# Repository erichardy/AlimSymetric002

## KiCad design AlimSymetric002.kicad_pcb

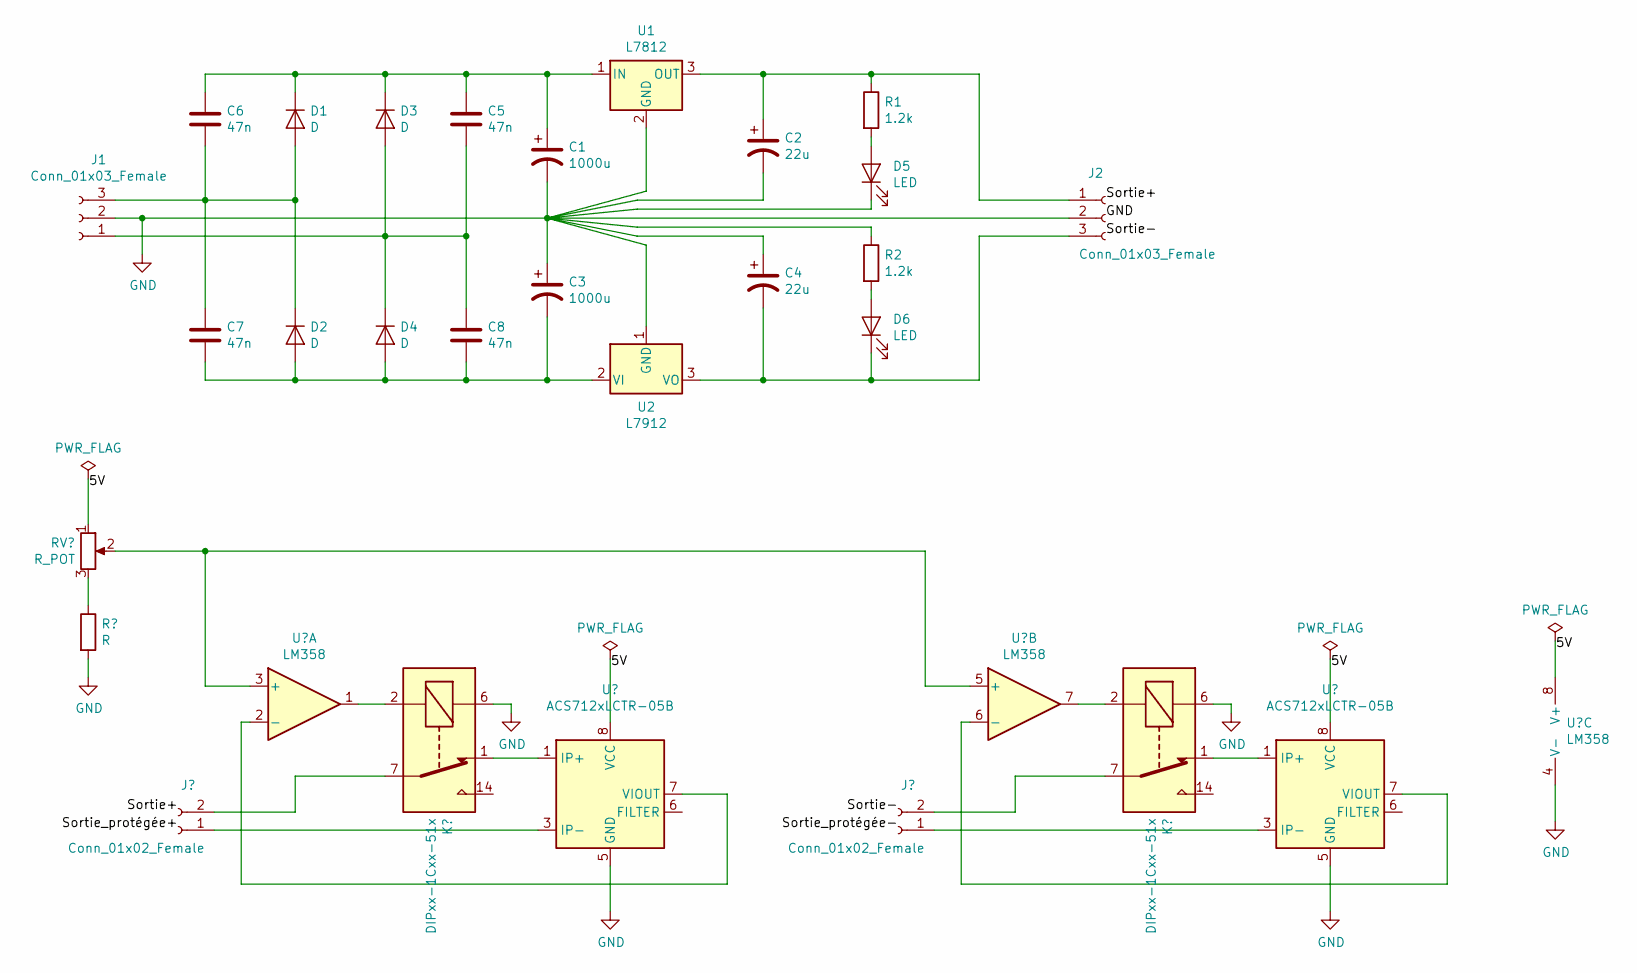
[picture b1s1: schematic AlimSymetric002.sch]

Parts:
C1, C3: 1000u; CP_Radial_D13.0mm_P5.00mm
C2, C4: 22u; CP_Radial_D4.0mm_P1.50mm
C5, C6, C7, C8: 47n; Cap47n-R_Axial_DIN0617_L17.0mm_D6.0mm_P5.08mm_Vertical
D1, D2, D3, D4: D; D_A-405_P12.70mm_Horizontal
D5, D6: LED; LED_D5.0mm
J1, J2: Conn_01x03_Female; TerminalBlock_Philmore_TB133_1x03_P5.00mm_Horizontal
R1, R2: 1.2k; R_Axial_DIN0516_L15.5mm_D5.0mm_P20.32mm_Horizontal
U1: L7812; TO-220-3_Vertical
U2: L7912; TO-220-3_Vertical

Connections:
GND: C1.2, C2.2, C3.1, C4.1, D5.1 (K), J1.2, J2.2, R2.1, U1.2 (GND), U2.1 (GND)
unnamed: C1.1, C5.1, C6.1, D1.1 (K), D3.1 (K), U1.1 (IN)
unnamed: C2.1, J2.1, R1.1, U1.3 (OUT)
unnamed: C3.2, C7.2, C8.2, D2.2 (A), D4.2 (A), U2.2 (VI)
unnamed: C4.2, D6.1 (K), J2.3, U2.3 (VO)
unnamed: C5.2, C8.1, D3.2 (A), D4.1 (K), J1.1
unnamed: C6.2, C7.1, D1.2 (A), D2.1 (K), J1.3
unnamed: D5.2 (A), R1.2
unnamed: D6.2 (A), R2.2

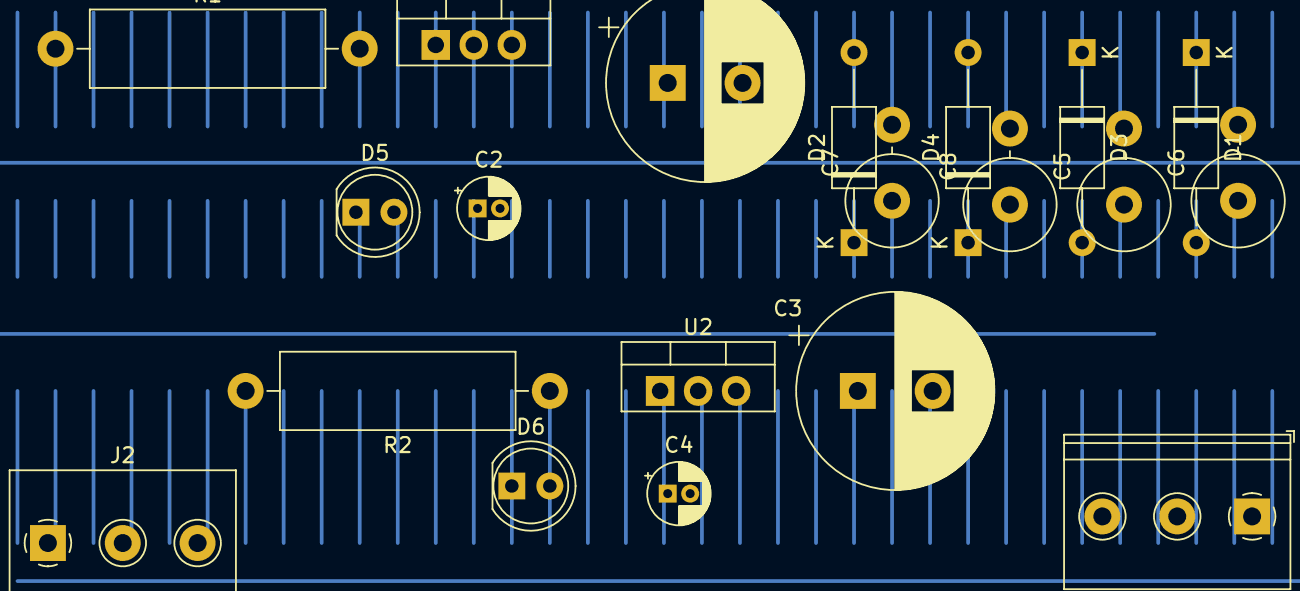
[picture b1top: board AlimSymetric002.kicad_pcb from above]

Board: 2 copper layers, 20 parts (0 on the bottom side), 9 nets.

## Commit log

2021-12-05 no modif
2021-12-07 adapter connector banane
